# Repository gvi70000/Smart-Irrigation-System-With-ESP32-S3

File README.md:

Introducing the Smart Irrigation System Controller Board powered by the ESP32-S3!

This hardware combines innovation and efficiency to revolutionize the way you manage your irrigation needs. Equipped with a host of advanced features, including an onboard BMP581 for precise weather data, support for up to 10 valve controls via relays, and seamless serial communication with a VL53L4CX sensor to accurately measure water levels in your well, this controller board is your key to achieving optimal irrigation and conserving valuable resources.

Say goodbye to guesswork and hello to intelligent, data-driven irrigation management, Welcome to the future of smart agriculture.

This feature-packed ESP32-S3-based Smart Irrigation System Controller Board is designed to streamline your irrigation management with unparalleled precision and control.

The board serves as the central hub for your irrigation system, seamlessly connecting and communicating with MQTT servers for efficient operation.

With 10 GPIO pins at your disposal, capable of driving up to 10 relays through 3V3 to 5V level shifters, you can effortlessly control the water flow in your irrigation system. The status of each output is visually presented using dedicated LEDs (L1 to L10 pins), providing real-time feedback to keep you informed.

For manual control of your valves, we've incorporated an analog input to read an array of push buttons. The voltage divider for the button array is thoughtfully designed for easy interfacing and intuitive operation.

The board also integrates Serial Port 1 of the ESP32-S3 to communicate with a VL53L4CX Time-Of-Flight sensor. This sensor plays a crucial role in monitoring water levels in your main reservoir or well, ensuring they remain within safe limits. The communication between the ESP32-S3 and the VL53L4CX is facilitated via an STM32F103 microcontroller, enhancing its capabilities. Notably, the power to the sensor is intelligently managed by the ESP32-S3 program to conserve energy.

To provide comprehensive environmental data, I've included a BMP581 pressure and temperature sensor on the I2C port. This allows you to access essential information such as atmospheric pressure and temperature. Additionally, the I2C port is open for additional device connections, provided that the I2C pull-up resistors are located on this controller board for your convenience.

For situations demanding higher current, the board offers a controlled output switch on S25V, directly connected to the 5V onboard power supply.

When it comes to programming, you have the flexibility to choose between the USB C port or the ESP32-S3 Serial Port 0 (Tx, Rx, 3V3, GND pins), making the process straightforward and accessible.

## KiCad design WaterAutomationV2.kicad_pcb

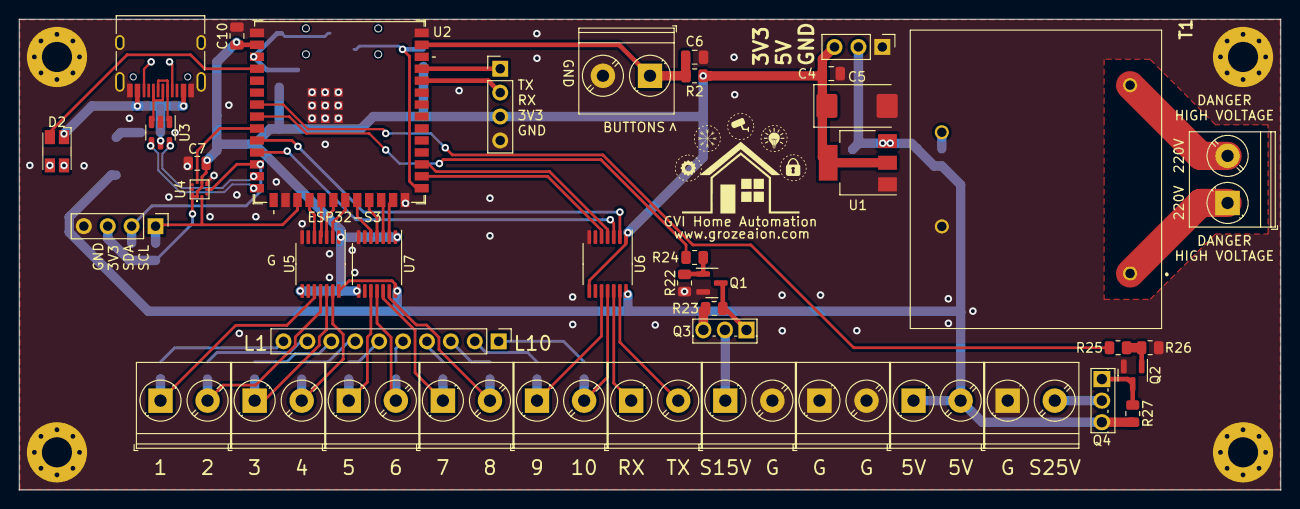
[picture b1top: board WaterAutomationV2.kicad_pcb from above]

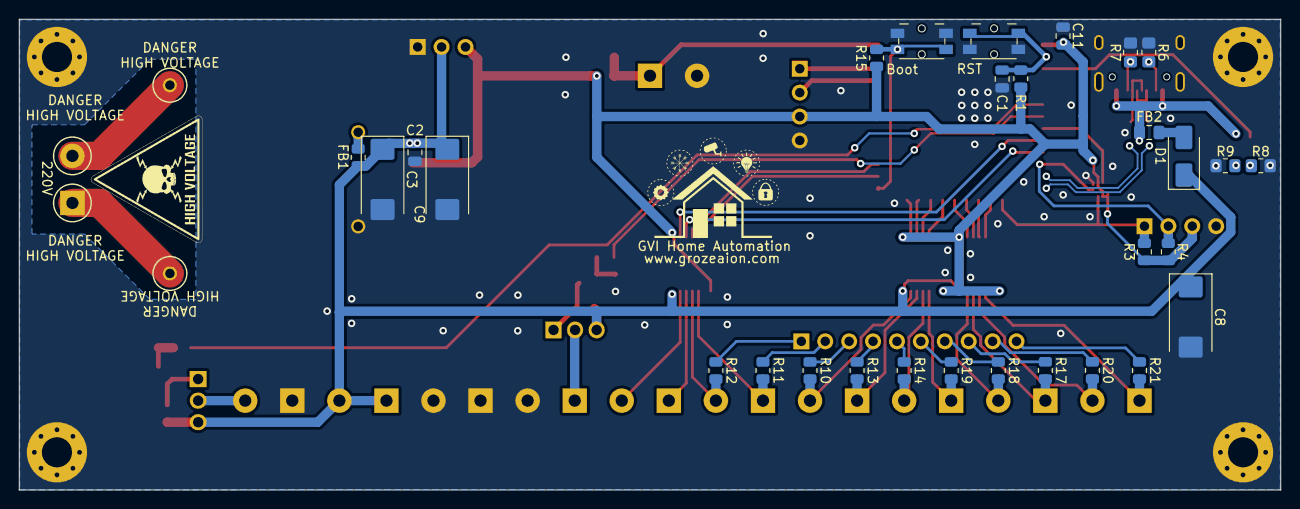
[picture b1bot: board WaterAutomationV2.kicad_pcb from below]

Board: 2 copper layers, 134.0 x 50.0 mm, 75 parts (29 on the bottom side), 67 nets.

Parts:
C1, C2, C4, C7, C10: 100n; C_0805_2012Metric
C3, C5, C8, C9: 22u; CP_EIA-7343-43_Kemet-X_Pad2.25x2.55mm_HandSolder
C6: C; C_0805_2012Metric
C11: 10u; C_0805_2012Metric
D1: MBRA340; D_SMA
D2: LED_Dual_AKKA; LED_Avago_PLCC4_3.2x2.8mm_CW
FB1: FerriteBead; R_0805_2012Metric
FB2: FerriteBead; C_0805_2012Metric_Pad1.18x1.45mm_HandSolder
H2, H3, H4, H5: MountingHole_Pad; MountingHole_3.2mm_M3_Pad_Via
J1, J3, J5, J7, J9, J10, J11, J13, J15, J17, J19, J20: Screw_Terminal_01x02; TerminalBlock_Phoenix_PT-1,5-2-5.0-H_1x02_P5.00mm_Horizontal
J2, J4: Conn_01x04; PinHeader_1x04_P2.54mm_Vertical
J6: Conn_01x03; PinHeader_1x03_P2.54mm_Vertical
J12: Conn_01x10; PinHeader_1x10_P2.54mm_Vertical
Q1, Q2: BSS138; SOT-23
Q3, Q4: IRFU9024NPBF; TO-251-3_Vertical
R1, R2, R15, R22, R23, R26, R27: 10k; R_0805_2012Metric
R3, R4: 2.2k; R_0805_2012Metric
R6, R7: 5.1k; R_0805_2012Metric_Pad1.20x1.40mm_HandSolder
R8: 100; R_0805_2012Metric_Pad1.20x1.40mm_HandSolder
R9: 220; R_0805_2012Metric_Pad1.20x1.40mm_HandSolder
R10, R11, R12, R13, R14, R17, R18, R19, R20, R21: 220; R_0805_2012Metric
R24, R25: 100; R_0805_2012Metric
SW1: RST; Panasonic_EVQPUM_EVQPUD
SW2: Boot; Panasonic_EVQPUM_EVQPUD
T1: 47152; MYRRA-47121
U1: LD1117S12TR_SOT223; SOT-223-3_TabPin2
U2: ESP32-S3-WROOM-1; ESP32-S3-WROOM-1U
U3: USBLC6-2SC6; SOT-23-6
U4: BMP581
U5, U6, U7: TXS0104E; TSSOP-14_4.4x5mm_P0.65mm
USB1: USB C; USB_C_Receptacle_HRO_TYPE-C-31-M-12

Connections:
+3.3V: C4.1, C5.1, C7.1, C10.1, C11.1, J2.3, J4.3, J6.3, R1.2, R2.1, R3.2, R4.2, R15.1, U1.2 (VO), U2.2 (3V3), U4.1 (VDDIO), U4.6 (CSB), U4.10 (VDD), U5.1 (VCCA), U5.8 (OE), U6.1 (VCCA), U6.8 (OE), U7.1 (VCCA), U7.8 (OE)
+5V: C2.1, C3.1, C8.1, C9.1, D1.1 (K), FB1.1, J6.2, J10.1, J10.2, Q3.3 (SOURCE), Q4.3 (SOURCE), R23.1, R27.1, U1.3 (VI), U5.14 (VCCB), U6.14 (VCCB), U7.14 (VCCB)
+5VD: D2.1 (A1), FB2.1, U3.5 (VBUS), USB1.A4 (VBUS), USB1.A9 (VBUS), USB1.B4 (VBUS), USB1.B9 (VBUS)
BOOT: R15.2, SW2.2, U2.27 (GPIO0/BOOT)
BUTTONS: C6.1, J5.1, R2.2, U2.39 (GPIO1/TOUCH1/ADC1_CH0)
CTRL_SEN1: R24.1, U2.8 (GPIO15/U0RTS/ADC2_CH4/XTAL_32K_P)
CTRL_SEN2: R25.1, U2.7 (GPIO7/TOUCH7/ADC1_CH6)
GND: C1.2, C2.2, C3.2, C4.2, C5.2, C6.2, C7.2, C8.2, C9.2, C10.2, C11.2, H2.1, H3.1, H4.1, H5.1, J1.1, J2.4, J4.4, J5.2, J6.1, J7.1, J7.2, J19.2, Q1.2 (S), Q2.2 (S), R6.1, R7.1, R8.1, R9.1, R22.1, R26.1, SW1.2, SW2.1, T1.9 (DC_OUTPUT_0V), U1.1 (GND), U2.1 (GND), U2.16 (GPIO46), U2.26 (GPIO45), U2.40 (GND), U2.41 (GND), U3.2 (GND), U4.3 (VSS_1), U4.5 (SDO), U4.8 (VSS_2), U4.9 (VSS_3), U5.7 (GND), U6.7 (GND), U7.7 (GND), USB1.A1 (GND), USB1.A12 (GND), USB1.B1 (GND), USB1.B12 (GND), USB1.S1 (Shell1)
INT: U2.9 (GPIO16/U0CTS/ADC2_CH5/XTAL_32K_N), U4.7 (INT)
LED: D2.4 (A2), U2.4 (GPIO4/TOUCH4/ADC1_CH3)
unnamed: D1.2 (A), FB2.2
unnamed: D2.2 (K1), R9.2
unnamed: D2.3 (K2), R8.2
unnamed: J3.1, T1.1 (AC_OR_DC_INPUT_1)
unnamed: J3.2, T1.5 (AC_OR_DC_INPUT_2)
unnamed: J12.1, R12.1
unnamed: J12.2, R11.1
unnamed: J12.3, R10.1
unnamed: J12.4, R13.1
unnamed: J12.5, R14.1
unnamed: J12.6, R19.1
unnamed: J12.7, R18.1
unnamed: J12.8, R17.1
unnamed: J12.9, R20.1
unnamed: J12.10, R21.1
unnamed: Q1.3 (D), Q3.1 (GATE), R23.2
unnamed: Q1.1 (G), R22.2, R24.2
unnamed: Q2.3 (D), Q4.1 (GATE), R27.2
unnamed: Q2.1 (G), R25.2, R26.2
unnamed: FB1.2, T1.7 (DC_OUTPUT_+V)
unnamed: U3.1 (I/O1), USB1.A7 (D-), USB1.B7 (D-)
unnamed: U3.3 (I/O2), USB1.A6 (D+), USB1.B6 (D+)
unnamed: R7.2, USB1.A5 (CC1)
unnamed: R6.2, USB1.B5 (CC2)
O1: J9.1, R21.2, U5.10 (B4)
O2: J9.2, R20.2, U5.11 (B3)
O3: J11.1, R17.2, U5.12 (B2)
O4: J11.2, R18.2, U5.13 (B1)
O5: J13.1, R19.2, U7.10 (B4)
O6: J13.2, R14.2, U7.11 (B3)
O7: J15.1, R13.2, U7.12 (B2)
O8: J15.2, R10.2, U7.13 (B1)
O9: J17.1, R11.2, U6.10 (B4)
O10: J17.2, R12.2, U6.11 (B3)
PWR_SEN1: J19.1, Q3.2 (DRAIN)
PWR_SEN2: J1.2, Q4.2 (DRAIN)
RST: C1.1, R1.1, SW1.1, U2.3 (EN)
RX0: J2.2, U2.36 (U0RXD/GPIO44/CLK_OUT2)
RX1: U2.11 (GPIO18/U1RXD/ADC2_CH7/CLK_OUT3), U6.3 (A2)
RX05: J20.1, U6.12 (B2)
SCL: J4.1, R3.1, U2.17 (GPIO9/TOUCH9/ADC1_CH8/FSPIHD/SUBSPIHD), U4.2 (SCK)
SDA: J4.2, R4.1, U2.12 (GPIO8/TOUCH8/ADC1_CH7/SUBSPICS1), U4.4 (SDI)
TX0: J2.1, U2.37 (U0TXD/GPIO43/CLK_OUT1)
TX1: U2.10 (GPIO17/U1TXD/ADC2_CH6), U6.2 (A1)
TX05: J20.2, U6.13 (B1)
USB_D+: U2.14 (GPIO20/U1CTS/ADC2_CH9/CLK_OUT1/USB_D+), U3.4 (I/O2)
USB_D-: U2.13 (GPIO19/U1RTS/ADC2_CH8/CLK_OUT2/USB_D-), U3.6 (I/O1)
V1: U2.18 (GPIO10/TOUCH10/ADC1_CH9/FSPICS0/FSPIIO4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), U5.5 (A4)
V2: U2.19 (GPIO11/TOUCH11/ADC2_CH0/FSPID/FSPIIO5/S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), U5.4 (A3)
V3: U2.20 (GPIO12/TOUCH12/ADC2_CH1/FSPICLK/FSPIIO6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), U5.3 (A2)
V4: U2.21 (GPIO13/TOUCH13/ADC2_CH2/FSPIQ/FSPIIO7/S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), U5.2 (A1)
V5: U2.22 (GPIO14/TOUCH14/ADC2_CH3/FSPIWP/FSPIDQS/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), U7.5 (A4)
V6: U2.23 (GPIO21), U7.4 (A3)
V7: U2.24 (GPIO47/SPICLK_P/SUBSPICLK_P_DIFF), U7.3 (A2)
V8: U2.25 (GPIO48/SPICLK_N/SUBSPICLK_N_DIFF), U7.2 (A1)
V9: U2.28 (SPIIO6/GPIO35/FSPID/SUBSPID), U6.5 (A4)
V10: U2.29 (SPIIO7/GPIO36/FSPICLK/SUBSPICLK), U6.4 (A3)

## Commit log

2024-02-25 LatestVersion
